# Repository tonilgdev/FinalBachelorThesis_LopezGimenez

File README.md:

# Antoni López Giménez's final bachelor's degree thesis repository

SEPTEMBER '23 UPDATE
> Currently, the repository is public and contains all the documents, code and hardware. The aim is to make it easily accessible.

ABSTRACT
> The aim of this project is to carry out a study of variations in human peripheral temperature as affected by stress, sleep and/or physical activity. To do this we have divided the project into two parts: the development of the measurement system and the assessment of this end. In order to be able to carry out the assessment correctly, we need to develop a system that can obtain the peripheral temperature of the subject to be studied and also know if it has been affected by physical activity. For this purpose we have developed a measurement system with a temperature sensor and an accelerometer as well as an RTC to be able to know at what instant of time the data have been collected. Finally, the assessment consists of the test subject taking the system with him/her for 2-3 days and returning it to download the data for analysis.

© 2021 Antoni López Giménez. All rights reserved.

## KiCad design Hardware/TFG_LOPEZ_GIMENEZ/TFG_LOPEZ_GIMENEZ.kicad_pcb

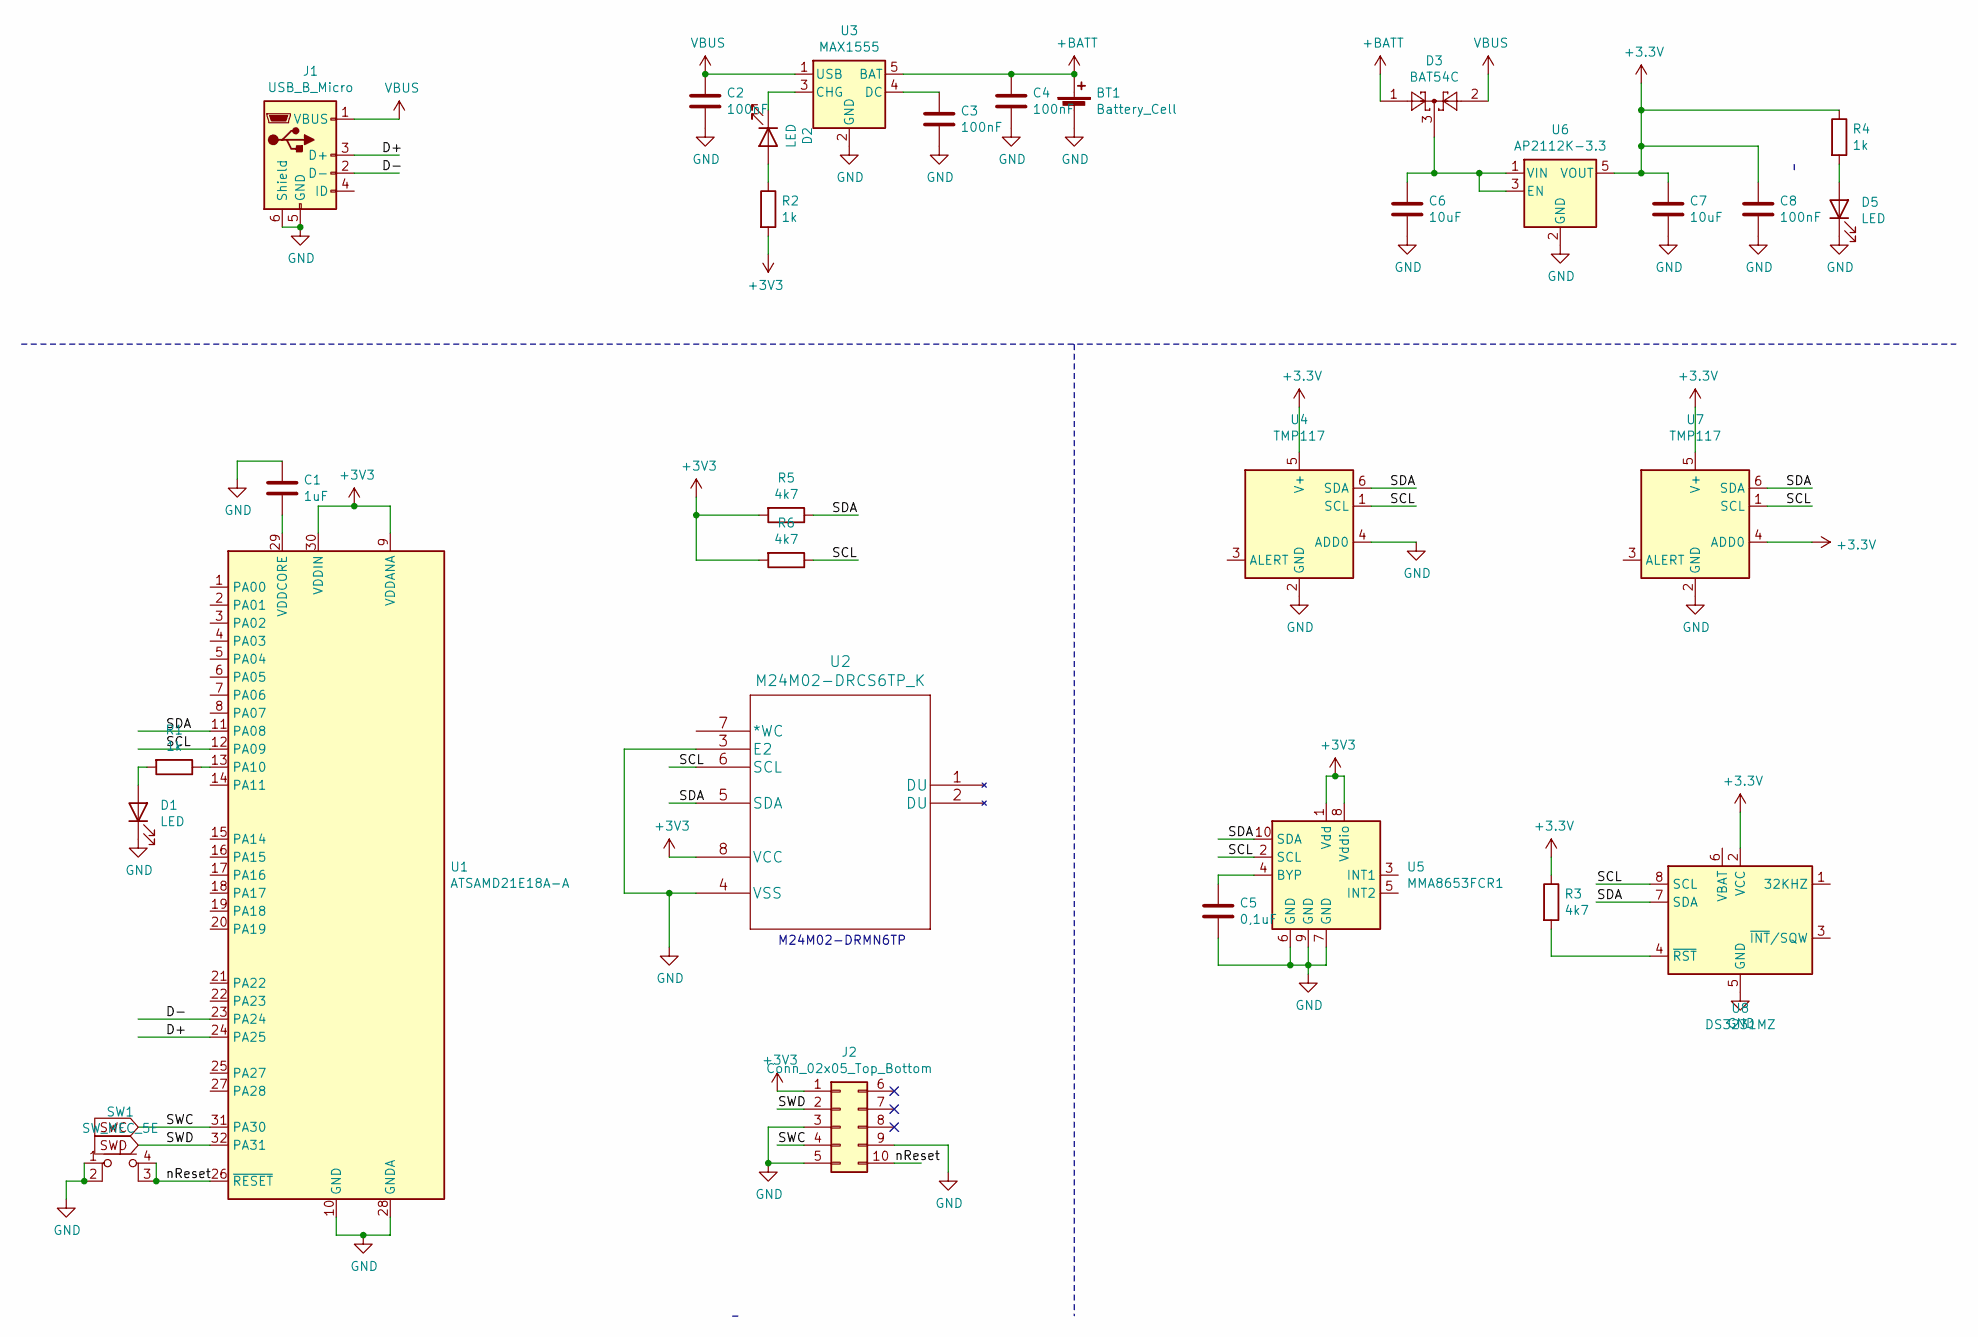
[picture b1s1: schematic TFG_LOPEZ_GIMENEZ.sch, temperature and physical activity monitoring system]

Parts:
BT1: Battery_Cell; PinHeader_1x02_P2.54mm_Vertical
C1: 1uF; C_0603_1608Metric_Pad1.08x0.95mm_HandSolder
C2, C3, C4, C8: 100nF; C_0603_1608Metric_Pad1.08x0.95mm_HandSolder
C5: 0,1uF; C_0603_1608Metric_Pad1.08x0.95mm_HandSolder
C6, C7: 10uF; C_0603_1608Metric_Pad1.08x0.95mm_HandSolder
D1, D2, D5: LED; LED_0603_1608Metric_Pad1.05x0.95mm_HandSolder
D3: BAT54C; SOT-23
J1: USB_B_Micro; USB_Micro-B_Molex-105017-0001
J2: Conn_02x05_Top_Bottom; PinHeader_2x05_P2.54mm_Vertical
R1, R2, R4: 1k; R_0603_1608Metric_Pad0.98x0.95mm_HandSolder
R3, R5, R6: 4k7; R_0603_1608Metric_Pad0.98x0.95mm_HandSolder
SW1: SW_MEC_5E; SW_SPST_Omron_B3FS-100xP
U1: ATSAMD21E18A-A; TQFP-32_7x7mm_P0.8mm
U2: M24M02-DRCS6TP_K; SOIC-8_3.9x4.9mm_P1.27mm
U3: MAX1555; SOT-23-5
U4, U7: TMP117; TMP116AIDRVR
U5: MMA8653FCR1; DFN-10_2x2mm_P0.4mm
U6: AP2112K-3.3; SOT-23-5
U8: DS3231MZ; SOIC-8_3.9x4.9mm_P1.27mm

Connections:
+BATT: BT1.1 (+), C4.1, D3.1, U3.5 (BAT)
/D+: J1.3 (D+), U1.24 (PA25)
/D-: J1.2 (D-), U1.23 (PA24)
/SCL: R6.1, U1.12 (PA09), U2.6 (SCL), U4.1 (SCL), U5.2 (SCL), U7.1 (SCL), U8.8 (SCL)
/SDA: R5.1, U1.11 (PA08), U2.5 (SDA), U4.6 (SDA), U5.10 (SDA), U7.6 (SDA), U8.7 (SDA)
/nReset: J2.10, SW1.3 (K), SW1.4 (A), U1.26 (~RESET)
GND: BT1.2 (-), C1.1, C2.2, C3.2, C4.2, C5.2, C6.2, C7.2, C8.2, D1.1 (K), D5.1 (K), J1.5 (GND), J1.6 (Shield), J2.3, J2.5, J2.9, SW1.1, SW1.2, U1.10 (GND), U1.28 (GND), U2.3 (E2), U2.4 (VSS), U3.2 (GND), U4.2 (GND), U4.4 (ADD0), U5.6 (GND), U5.7 (GND), U5.9 (GND), U6.2 (GND), U7.2 (GND), U8.5 (GND)
unnamed: C1.2, U1.29 (VDDCORE)
unnamed: C3.1, U3.4 (DC)
unnamed: C5.1, U5.4 (BYP)
unnamed: C6.1, D3.3, U6.1 (VIN), U6.3 (EN)
unnamed: D1.2 (A), R1.2
unnamed: D2.1 (K), U3.3 (CHG)
unnamed: D2.2 (A), R2.1
unnamed: D5.2 (A), R4.2
unnamed: R1.1, U1.13 (PA10)
unnamed: R3.2, U8.4 (~RST)
SWC: J2.4, U1.31 (PA30)
SWD: J2.2, U1.32 (PA31)
VBUS: C2.1, D3.2, J1.1 (VBUS), U3.1 (USB)

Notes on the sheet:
M24M02-DRMN6TP

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
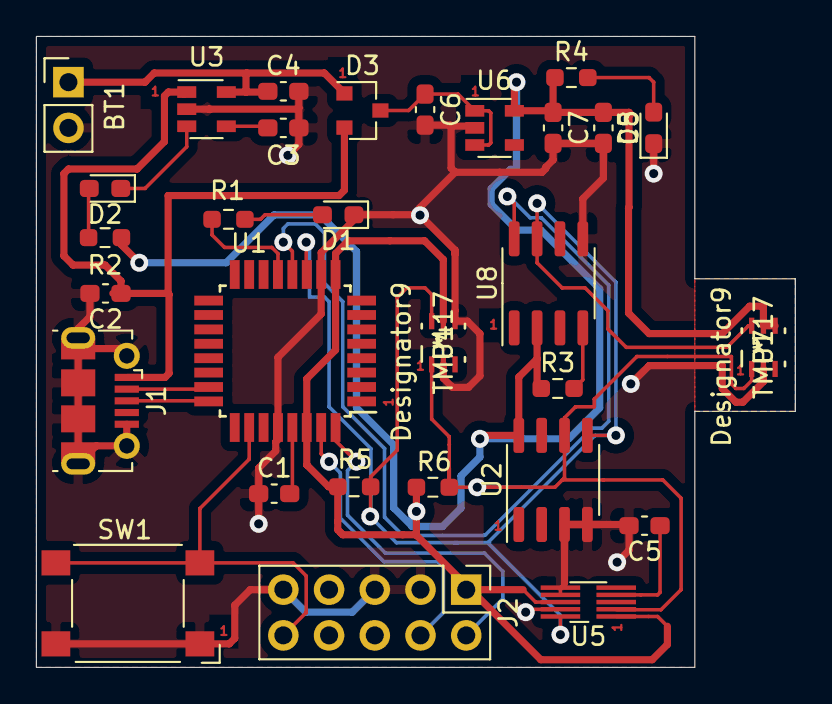
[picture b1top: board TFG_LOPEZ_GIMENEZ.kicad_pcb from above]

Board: 2 copper layers, 42.2 x 35.1 mm, 30 parts (0 on the bottom side), 21 nets.

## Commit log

2023-10-07 Repository creation and REAME update

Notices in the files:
parts and their libraries:
Copyright 2016 Accelerated Designs. All rights reserved.
